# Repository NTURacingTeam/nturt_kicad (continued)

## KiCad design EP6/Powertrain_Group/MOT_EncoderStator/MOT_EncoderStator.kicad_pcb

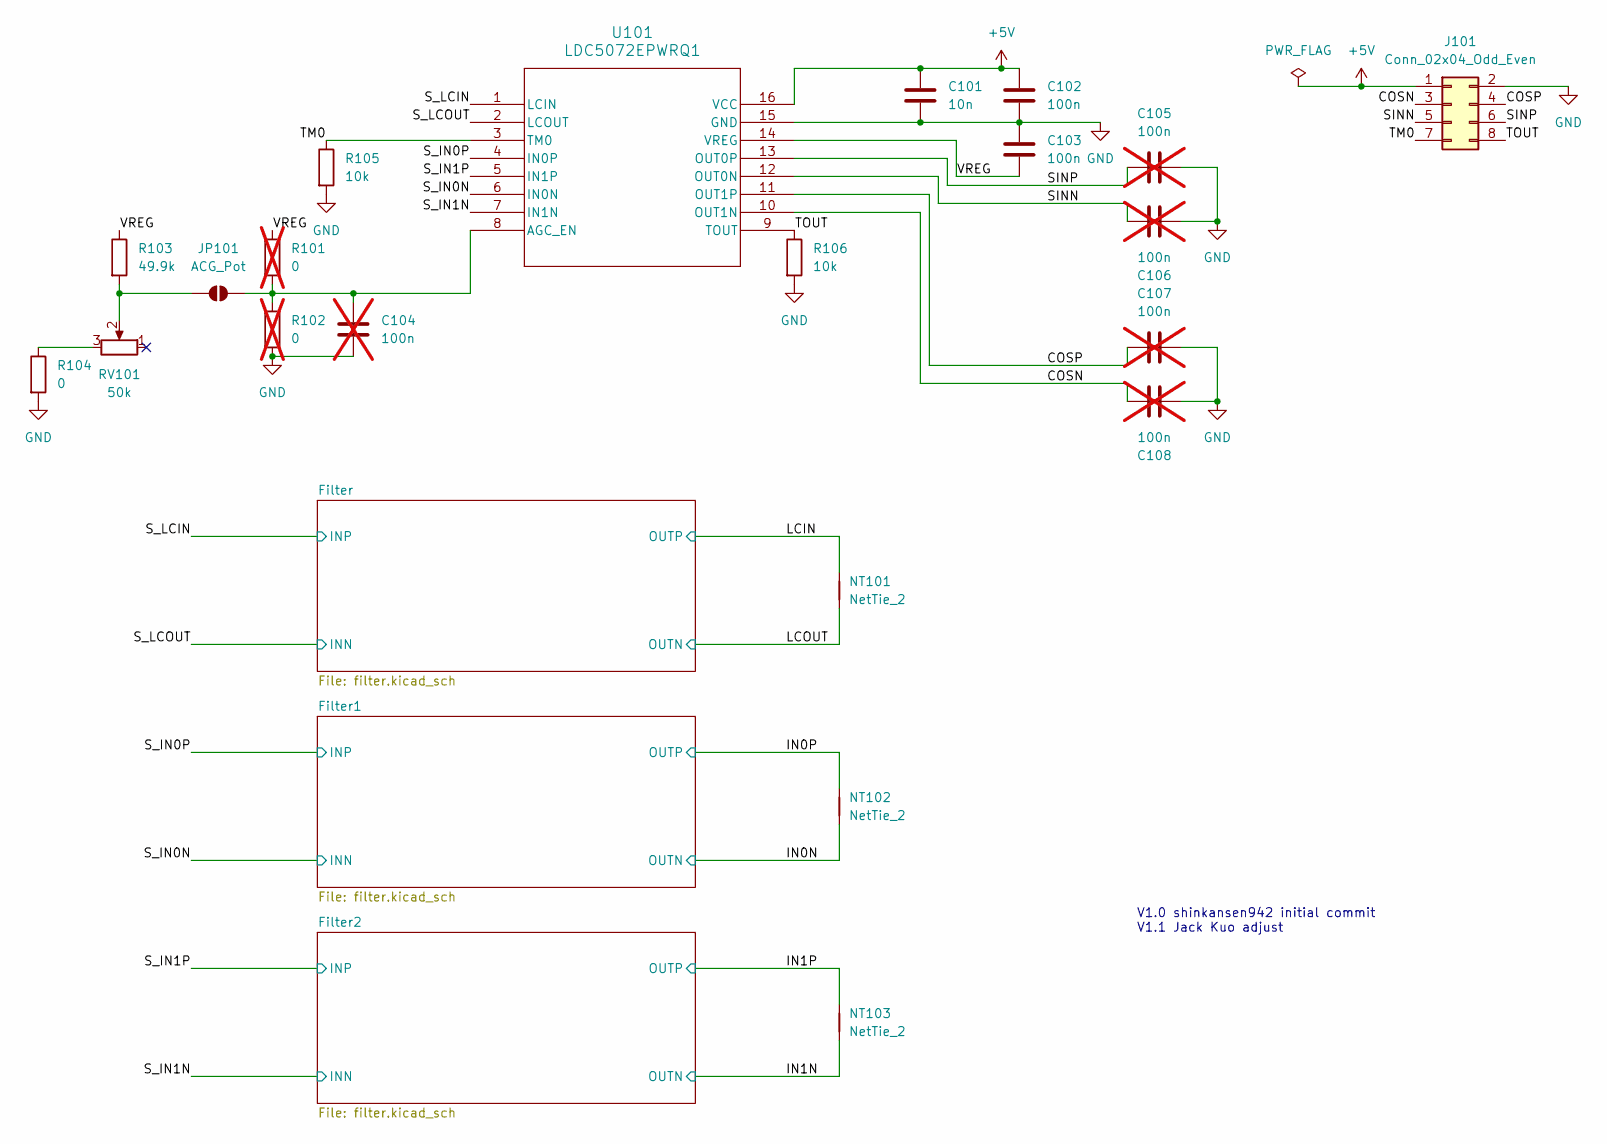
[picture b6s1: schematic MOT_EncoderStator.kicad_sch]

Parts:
C101: 10n; C_0402_1005Metric
C102, C103: 100n; C_0402_1005Metric
C104, C105, C106, C107, C108: 100n; C_0402_1005Metric; not fitted
J101: Conn_02x04_Odd_Even; PinHeader_2x04_P2.54mm_Vertical_SMD
JP101: ACG_Pot; SolderJumper-2_P1.3mm_Open_RoundedPad1.0x1.5mm
NT101, NT102, NT103: NetTie_2; NetTie-2_SMD_Pad0.5mm
R101, R102: 0; R_0603_1608Metric; not fitted
R103: 49.9k; R_0402_1005Metric
R104: 0; R_0402_1005Metric
R105, R106: 10k; R_0402_1005Metric
RV101: 50k; Potentiometer_Bourns_3224W_Vertical
U101: LDC5072EPWRQ1; TSSOP16-PW_TEX

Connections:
+5V: C101.1, C102.1, J101.1, U101.16 (VCC)
/COSN: C108.2, J101.3, U101.10 (OUT1N)
/COSP: C107.1, J101.4, U101.11 (OUT1P)
/IN0N: NT102.1; also elsewhere on the board
/IN0P: NT102.2; also elsewhere on the board
/IN1N: NT103.1; also elsewhere on the board
/IN1P: NT103.2; also elsewhere on the board
/LCIN: NT101.2; also elsewhere on the board
/LCOUT: NT101.1; also elsewhere on the board
/SINN: C106.2, J101.5, U101.12 (OUT0N)
/SINP: C105.1, J101.6, U101.13 (OUT0P)
/S_IN0N: U101.6 (IN0N); also elsewhere on the board
/S_IN0P: U101.4 (IN0P); also elsewhere on the board
/S_IN1N: U101.7 (IN1N); also elsewhere on the board
/S_IN1P: U101.5 (IN1P); also elsewhere on the board
/S_LCIN: U101.1 (LCIN); also elsewhere on the board
/S_LCOUT: U101.2 (LCOUT); also elsewhere on the board
/TM0: J101.7, R105.1, U101.3 (TM0)
/TOUT: J101.8, R106.1, U101.9 (TOUT)
/VREG: C103.2, R101.1, R103.1, U101.14 (VREG)
GND: C101.2, C102.2, C103.1, C104.2, C105.2, C106.1, C107.2, C108.1, J101.2, R102.2, R104.2, R105.2, R106.2, U101.15 (GND); also elsewhere on the board
unnamed: JP101.1 (A), R103.2, RV101.2
unnamed: C104.1, JP101.2 (B), R101.2, R102.1, U101.8 (AGC_EN)
unnamed: R104.1, RV101.3

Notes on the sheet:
V1.0 shinkansen942 initial commit V1.1 Jack Kuo adjust

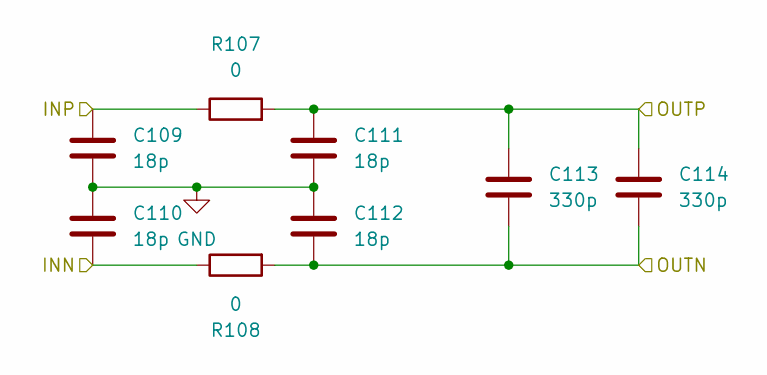
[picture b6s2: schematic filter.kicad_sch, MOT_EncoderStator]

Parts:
C109, C110, C111, C112: 18p; C_0402_1005Metric
C113, C114: 330p; C_0402_1005Metric
R107, R108: 0; R_0402_1005Metric

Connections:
/LCIN: C111.1, C113.1, C114.1, R107.2; also elsewhere on the board
/LCOUT: C112.2, C113.2, C114.2, R108.2; also elsewhere on the board
/S_LCIN: C109.1, R107.1; also elsewhere on the board
/S_LCOUT: C110.2, R108.1; also elsewhere on the board
GND: C109.2, C110.1, C111.2, C112.1; also elsewhere on the board

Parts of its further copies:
C115, C116, C117, C118, C121, C122, C123, C124: 18p; C_0402_1005Metric
C119, C120, C125, C126: 330p; C_0402_1005Metric
R109, R110, R111, R112: 0; R_0402_1005Metric

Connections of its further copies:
/IN0N: C118.2, C119.2, C120.2, R110.2; also elsewhere on the board
/IN0P: C117.1, C119.1, C120.1, R109.2; also elsewhere on the board
/IN1N: C124.2, C125.2, C126.2, R112.2; also elsewhere on the board
/IN1P: C123.1, C125.1, C126.1, R111.2; also elsewhere on the board
/S_IN0N: C116.2, R110.1; also elsewhere on the board
/S_IN0P: C115.1, R109.1; also elsewhere on the board
/S_IN1N: C122.2, R112.1; also elsewhere on the board
/S_IN1P: C121.1, R111.1; also elsewhere on the board
GND: C115.2, C116.1, C117.2, C118.1, C121.2, C122.1, C123.2, C124.1; also elsewhere on the board

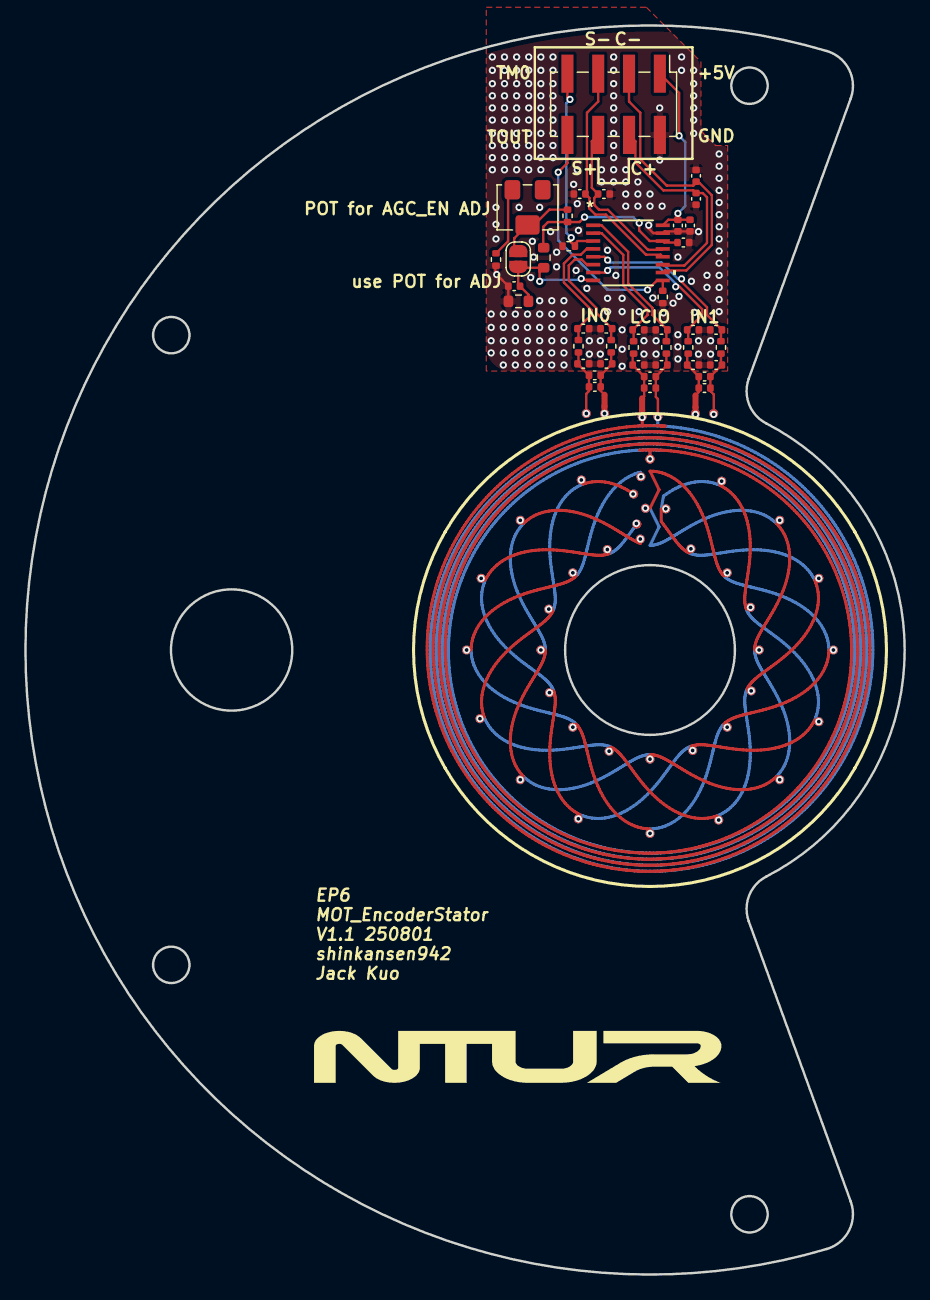
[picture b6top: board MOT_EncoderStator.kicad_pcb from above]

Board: 4 copper layers, 72.5 x 103.0 mm, 45 parts (0 on the bottom side), 24 nets.
